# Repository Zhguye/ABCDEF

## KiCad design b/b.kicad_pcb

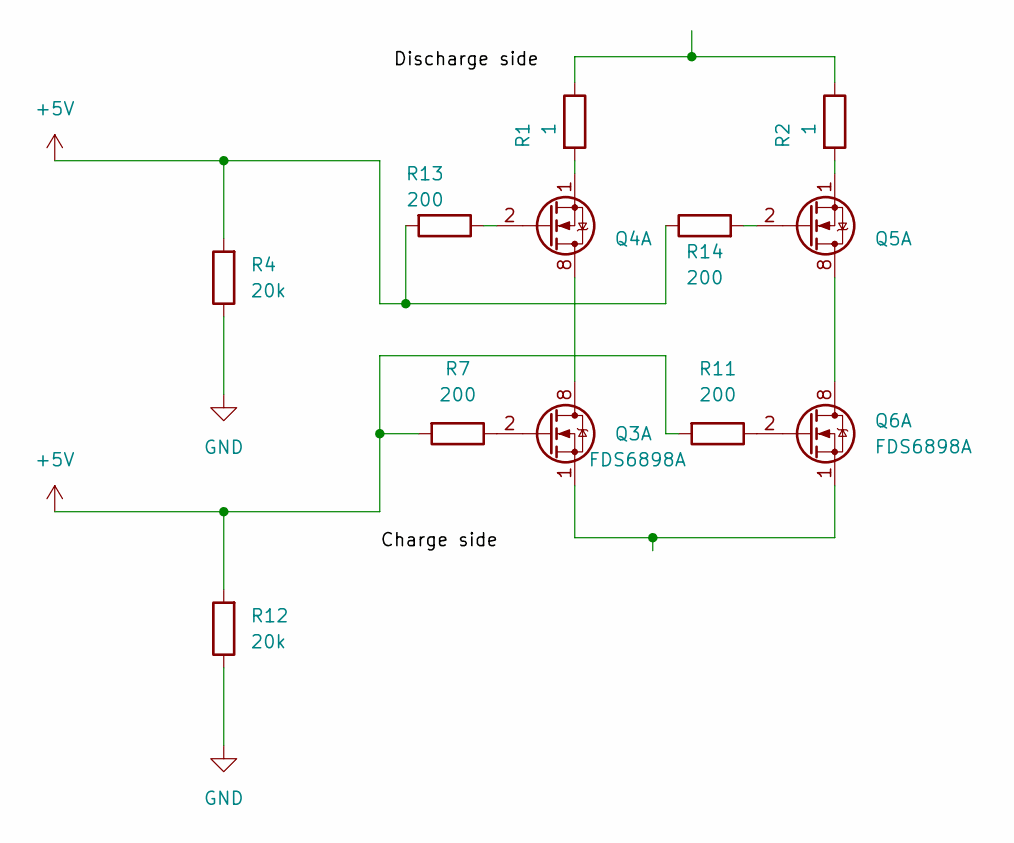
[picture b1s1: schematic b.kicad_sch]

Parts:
Q3, Q4, Q5, Q6: FDS6898A; SOIC-8_3.9x4.9mm_P1.27mm
R1, R2: 1; R_0603_1608Metric
R4, R12: 20k; R_0603_1608Metric
R7, R11, R13, R14: 200; R_0603_1608Metric

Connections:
+5V: R4.2, R7.2, R11.2, R12.2, R13.2, R14.1
GND: R4.1, R12.1
unnamed: Q3.7 (D1), Q3.8 (D1), Q4.7 (D1), Q4.8 (D1)
unnamed: Q3.2 (G1), R7.1
unnamed: Q3.1 (S1), Q6.1 (S1)
unnamed: Q4.2 (G1), R13.1
unnamed: Q4.1 (S1), R1.2
unnamed: Q5.7 (D1), Q5.8 (D1), Q6.7 (D1), Q6.8 (D1)
unnamed: Q5.2 (G1), R14.2
unnamed: Q5.1 (S1), R2.2
unnamed: Q6.2 (G1), R11.1
unnamed: R1.1, R2.1

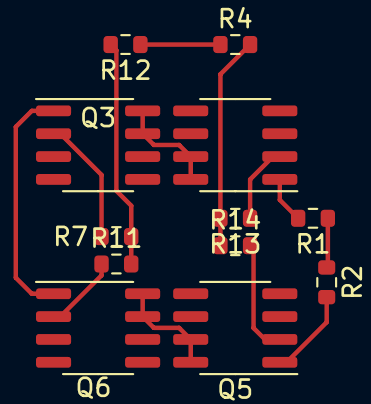
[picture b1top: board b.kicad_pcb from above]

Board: 2 copper layers, 12 parts (0 on the bottom side), 12 nets.

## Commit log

2023-09-20 Create a
